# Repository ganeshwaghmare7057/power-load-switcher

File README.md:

# power-load-switcher_project
Description:  It is mainly designed for battery and main power switcher. I used ESP32 controller and thermistor (sensor). Collecting the different module like RS-485, TP4056, ADC, LM2596, transformer, bridge rectifier (W10M) and one channel relay.

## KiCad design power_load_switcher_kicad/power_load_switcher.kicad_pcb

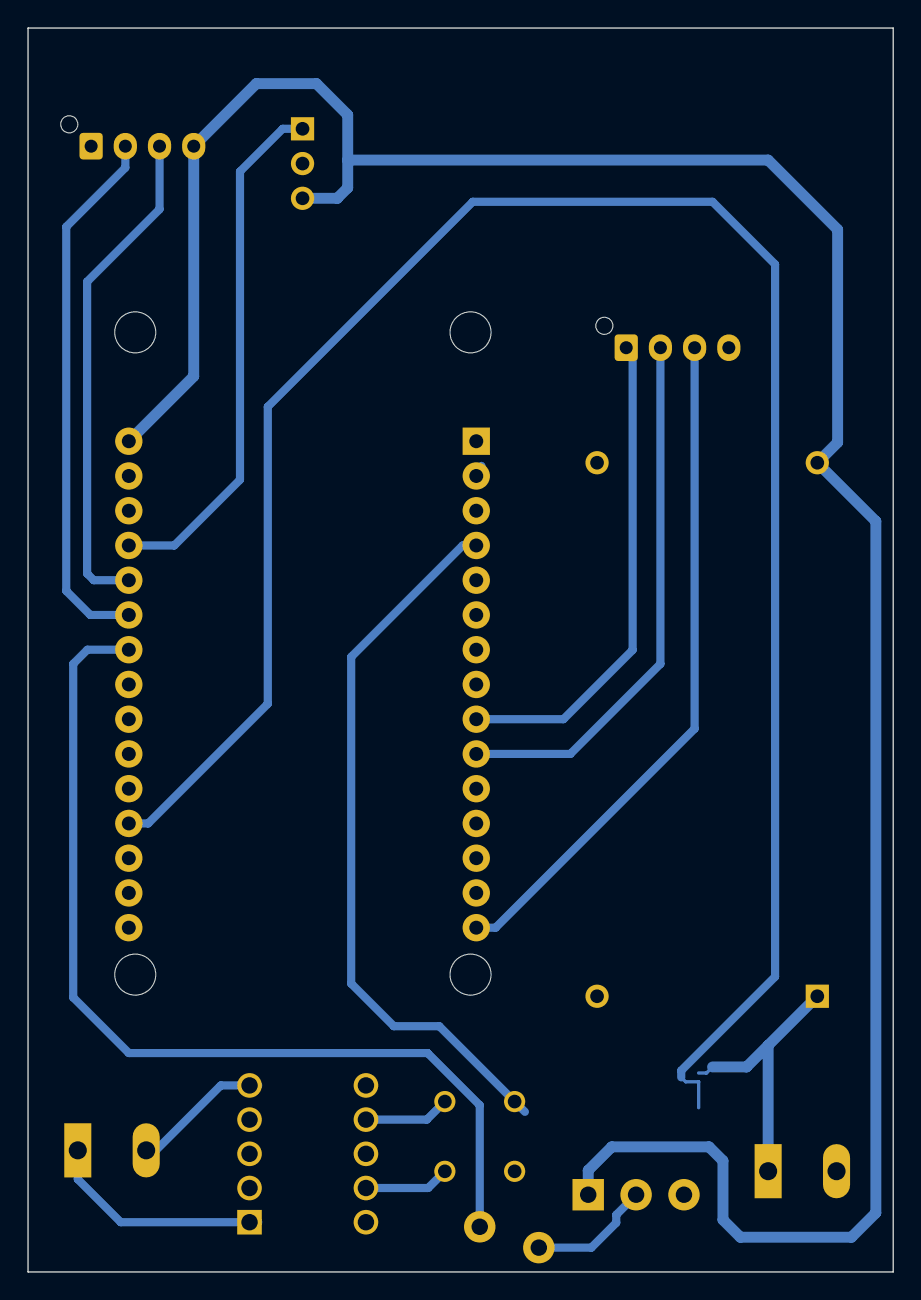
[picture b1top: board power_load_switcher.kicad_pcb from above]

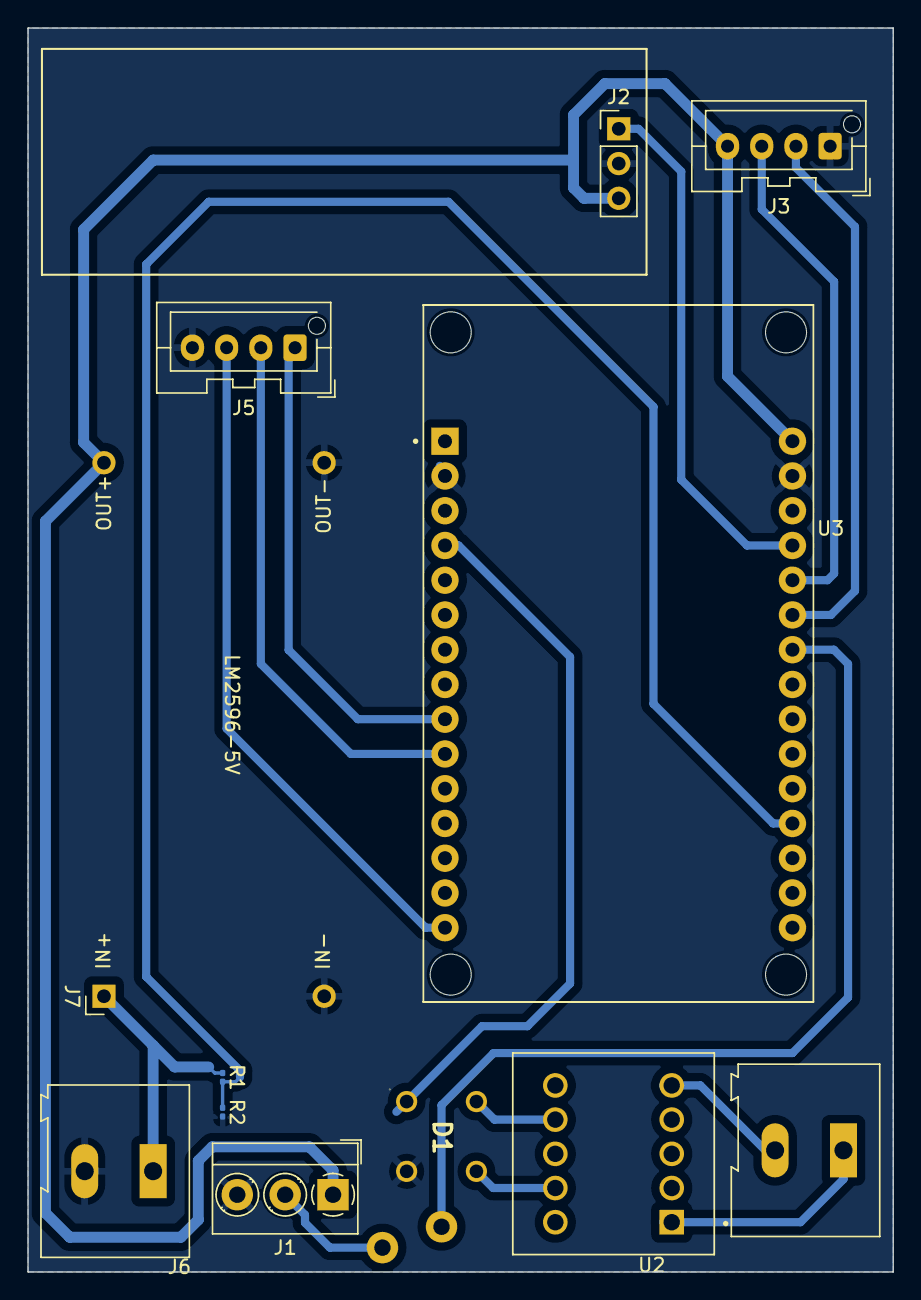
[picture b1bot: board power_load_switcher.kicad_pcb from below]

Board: 2 copper layers, 63.2 x 90.9 mm, 12 parts (12 on the bottom side), 16 nets.

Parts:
D1: D_Bridge_+-AA; WOM
J1: MCP9700; TerminalBlock_MetzConnect_Type059_RT06303HBWC_1x03_P3.50mm_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
J2: RELAY_CONNECTOR; PinHeader_1x03_P2.54mm_Vertical
J3: LCD; JST_XA_B04B-XASK-1-A_1x04_P2.50mm_Vertical
J4: AC SUPPLY; TerminalBlock_Altech_AK300-2_P5.00mm
J5: BUTTONS; JST_XA_B04B-XASK-1-A_1x04_P2.50mm_Vertical
J6: battery(+60V); TerminalBlock_Altech_AK300-2_P5.00mm
J7: LM2596-5V; LM2596
R1: 57; R_0201_0603Metric
R2: 3.3; R_0201_0603Metric
U2: EE13_6_6; BOBBIN_EE13_6_6
U3: ESP32-DEVKIT-V1; MODULE_ESP32_DEVKIT_V1

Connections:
+5V: J1.1, J2.3, J3.4, J7.3 (OUT+), U3.30 (VIN)
+BATT: J6.1, J7.1 (IN+), R1.1
GND: D1.2 (-), J1.3, J2.2, J3.1, J5.4, J6.2, J7.2 (IN-), J7.4 (OUT-), R2.2, U3.2 (GND), U3.29 (GND)
MAINS Monitoring: D1.1 (+), U3.4 (D2)
MCP9700 - DATA: J1.2, U3.24 (D26)
unnamed: D1.3, U2.9
unnamed: D1.4, U2.7
unnamed: J4.1, U2.1
unnamed: J4.2, U2.5
unnamed: R1.2, R2.1, U3.19 (D34)
Push button - DOWN: J5.1, U3.9 (D18)
Push button - UP: J5.3, U3.15 (D23)
Push button- ENTER: J5.2, U3.10 (D19)
RELAY: J2.1, U3.27 (D12)
SCL: J3.2, U3.25 (D27)
SDA: J3.3, U3.26 (D14)
